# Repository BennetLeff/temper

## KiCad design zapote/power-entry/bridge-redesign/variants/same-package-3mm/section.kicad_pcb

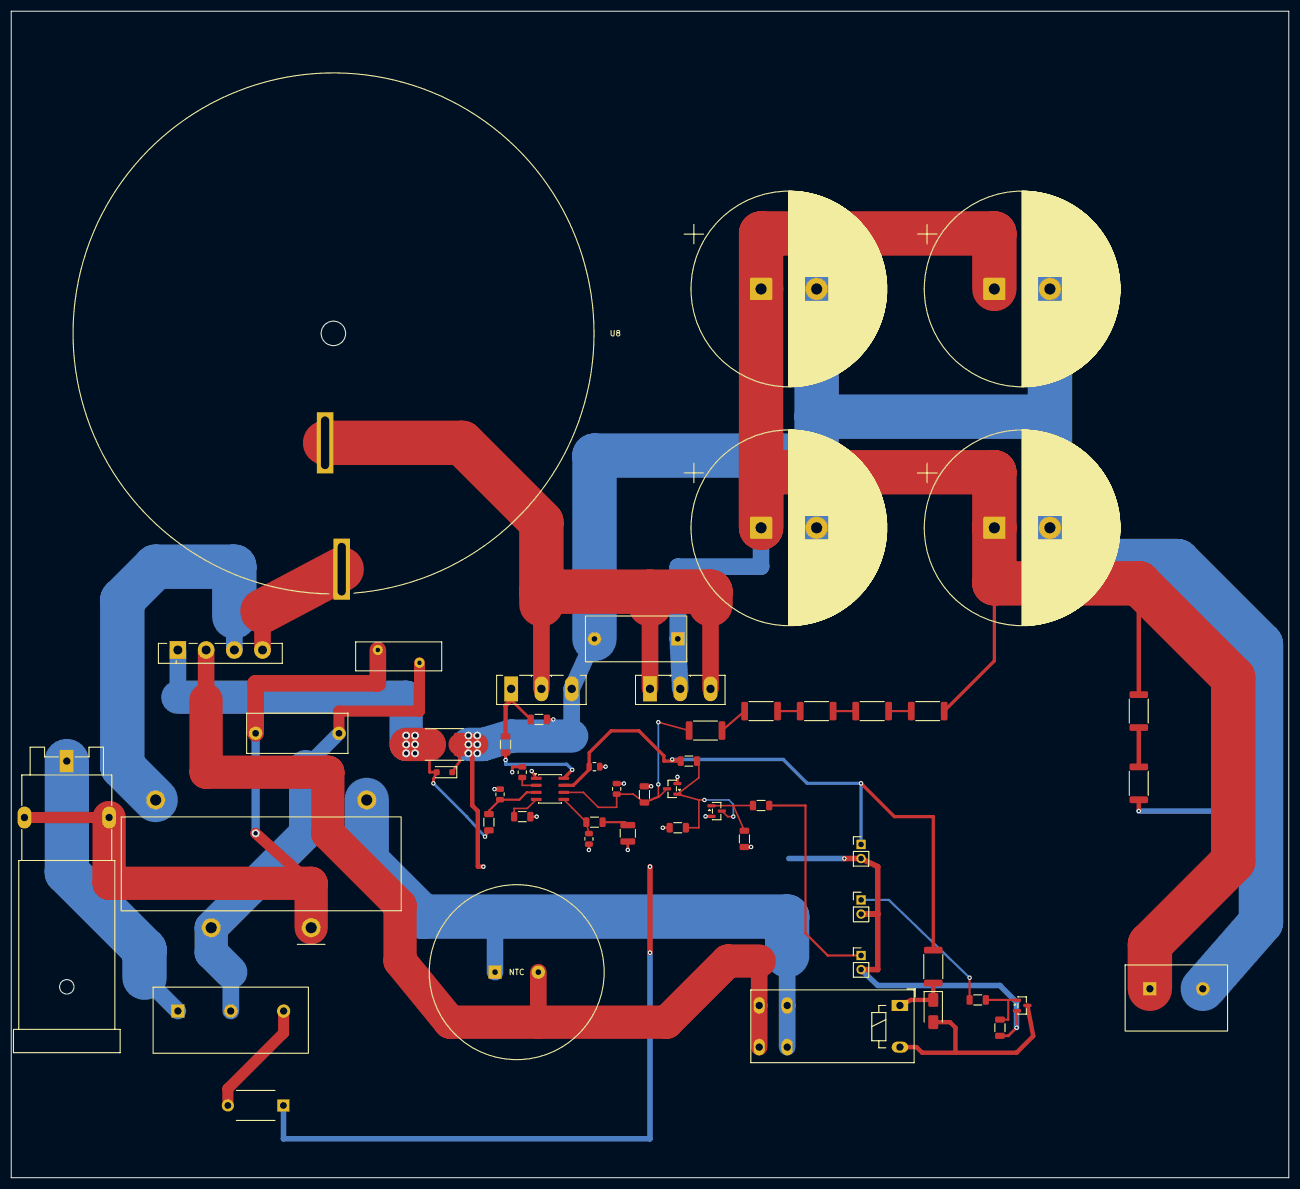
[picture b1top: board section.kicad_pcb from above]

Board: 2 copper layers, 230.0 x 210.0 mm, 54 parts (0 on the bottom side), 33 nets.

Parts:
U1: GBU2510A; Diode_Bridge_GBU2510
U2: 0031.2510; Fuseholder_Cylinder-5x20mm_Schurter_FUP_0031.2510_Horizonta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
U3: B82726S2163N030; CMC_B82726S
U4: SL32 10015; SL32_10015
U5: RT33K012; Relay_SPST_Schrack-RT33K012
U6: 0.22uF; C_Rect_L18.0mm_W7.0mm_P15.00mm_FKS3_FKP3
U7: V150LA10AP; RV_Disc_D15.5mm_W5.2mm_P7.5mm
U8: 760800301; L_Wurth_WE-TORPFC-T75
U9: STW65N65DM2; TO-247-3_Vertical
U10: C3D20065D; TO-247-3_Vertical
U11: UCC28180D; SOIC-8_3.9x4.9mm_P1.27mm
U12: 10mohm; WSL2726R0100FEA
U13: 10ohm; R_1206_3216Metric
U14: 10kohm; R_1206_3216Metric
U15, U50: 1kohm; R_1206_3216Metric
U16, U48, U49, U51: 100kohm; R_1206_3216Metric
U17: 91ohm; R_2512_6332Metric
U18: 220ohm; R_1206_3216Metric
U19: 16.2kohm; R_1206_3216Metric
U20, U21, U22, U23, U24: 200kohm; R_2512_6332Metric
U25: 13kohm; R_1206_3216Metric
U26: 40.2kohm; R_1206_3216Metric
U27: 1uF; C_0805_2012Metric
U28: 2.7nF; C_0805_2012Metric
U29: 4.7uF; C_1210_3225Metric
U30: 220nF; C_0805_2012Metric
U31: 1nF; C_0805_2012Metric
U32: 680pF; C_0805_2012Metric
U33, U46, U47: AO3400A; SOT-23
U34: SS14; D_SMA
U35: BAT54H,115; D_SOD-123F
U36, U37, U38, U39: 560uF; CP_Radial_D35.0mm_P10.00mm_SnapIn
U40: 470nF; B32672P6474K000
U41: 1nF; C_Disc_Vishay_VY1102M31Y5UQ63V0
U42: 1714984; Phoenix_1714984
U43, U44, U45: 61300211121; PinHeader_1x02_P2.54mm_Vertical
U52: 1714971; Phoenix_1714971
U53, U54: 150kohm; R_2512_6332Metric

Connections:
AC_L_RECTIFIED_INPUT: U2.1, U42.1
AC_N_RECTIFIED_INPUT: U3.2, U6.2, U7.2, U42.2
AUX_15V_IN: U11.7, U17.1, U27.1, U43.1, U49.1
HOT_PERMIT_EXTERNAL: U45.1, U50.1
PE_CHASSIS: U41.2, U42.3
PFC_BUS_MINUS: U9.3, U11.1, U12.1, U14.2, U16.2, U19.2, U25.2, U27.2, U28.2, U29.2, U30.2, U31.2, U32.2, U33.2, U35.1, U36.2, U37.2, U38.2, U39.2, U40.2, U41.1, U43.2, U44.2, U45.2, U46.2, U47.2, U48.2, U51.2, U52.2, U54.2
PFC_BUS_PLUS_390V: U10.2, U20.1, U36.1, U37.1, U38.1, U39.1, U40.1, U52.1, U53.1
RELAY_BYPASS_CTRL: U15.1, U44.1
a1: U8.2, U9.2, U10.1, U10.3
ac1: U1.2, U4.2, U5.3
ac2: U1.3, U3.3
bleeder1-p2: U53.2, U54.1
coil1: U5.1, U17.2, U34.1
coil2: U5.2, U33.3, U34.2
freq: U11.4, U19.1
gate: U11.8, U13.1
icomp: U11.2, U28.1
isense: U11.3, U18.1, U31.1
l1: U2.2, U3.1, U6.1, U7.1
l2: U3.4, U4.1, U5.4
minus: U1.1, U12.2, U18.2, U35.2
plus: U1.4, U8.1
q_boost-g: U9.1, U13.2, U14.1
q_inhibit-g: U46.1, U47.3, U48.1, U49.2
q_permit-g: U47.1, U50.2, U51.1
r_relay_gate-g: U15.2, U16.1, U33.1
r_vcomp-p2: U26.2, U29.1
r_vtop2-p2: U21.2, U22.1
r_vtop3-p2: U22.2, U23.1
r_vtop4-p2: U23.2, U24.1
r_vtop-p2: U20.2, U21.1
vcomp: U11.5, U26.1, U30.1
vsense: U11.6, U24.2, U25.1, U32.1, U46.3
